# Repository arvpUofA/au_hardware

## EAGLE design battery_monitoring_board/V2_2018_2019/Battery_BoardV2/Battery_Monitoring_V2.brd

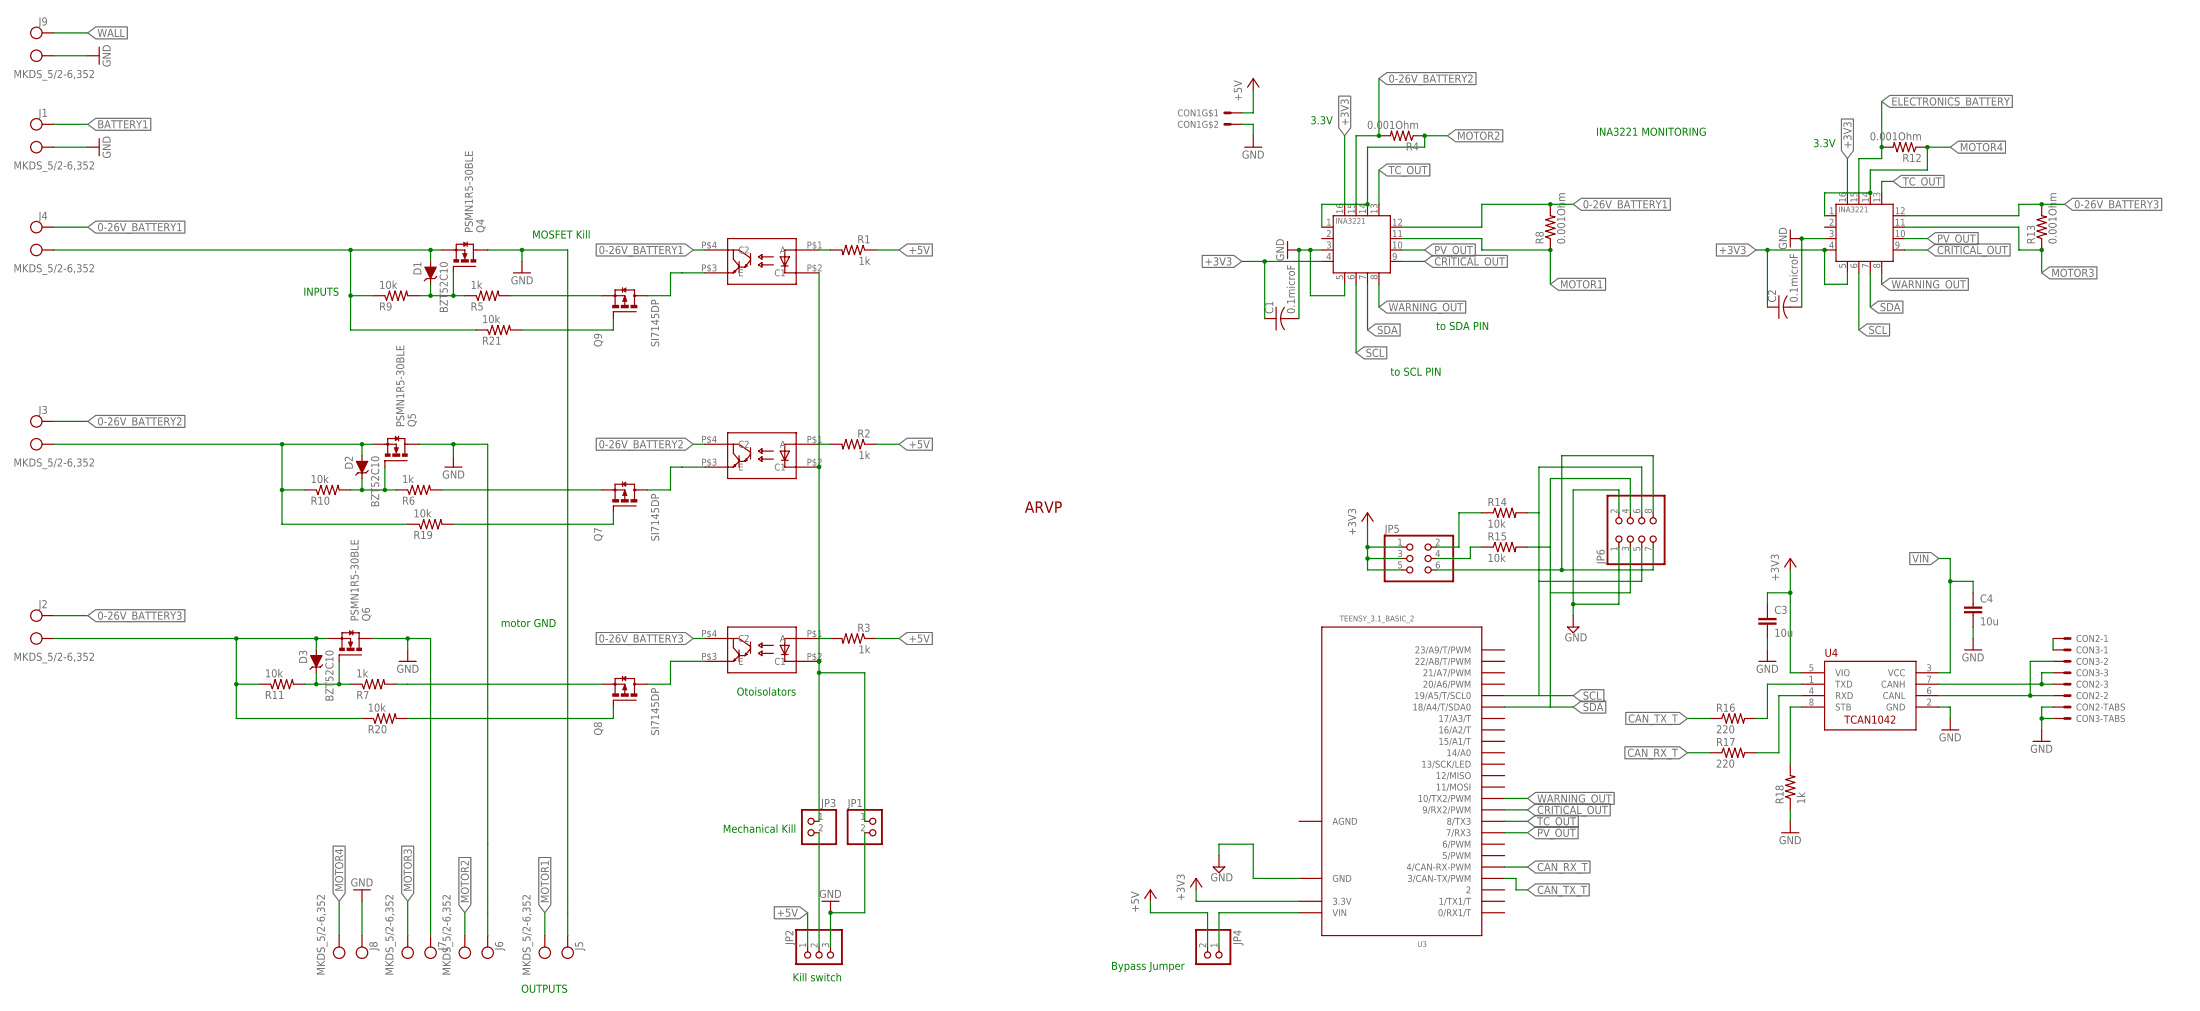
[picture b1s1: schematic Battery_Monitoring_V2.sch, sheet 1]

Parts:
ARVP1: ARVP_LOGO; ARVP
C1, C2: 0.1microF; C2012
C3, C4: 10u; C0805
CON1: MOLEX_5566-2; 5566-2
CON2, CON3: SM03B-GHS-TB
D1, D2, D3: BZT52C10; SOD-123
J1, J2, J3, J4, J5, J6, J7, J8, J9: MKDS_5/2-6,352; MKDS_5/2-6,35
JP1, JP3, JP4: PINHD-1X2; 1X02
JP2: PINHD-1X3; 1X03
JP5: PINHD-2X3; 2X03
JP6: PINHD-2X4; 2X04
Q1, Q2, Q3: TCLD1000CT; SOP-4L
Q4, Q5, Q6: PSMN1R5-30BLE; SOT404/D2PAK
Q7, Q8, Q9: SI7145DP; SO-8/PPAK/TEST; MPN SI7145DP-T1-GE3
R1, R2, R3, R18: 1k; R0805
R4, R8, R12, R13: 0.001Ohm; 3920
R5, R6, R7: 1k; M1206
R9, R10, R11: 10k; M1206
R14, R15: 10k; R1206
R16, R17: 220; R0805
R19, R20, R21: 10k; M1206; MPN RC0603FR-0710KL
U1, U2: INA3221.; HVQFN16_4X4
U3: TEENSY_3.1_BASIC_2
U4: TCAN1042HVDR; SO-8

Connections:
0-26V_BATTERY1: J4.2 (KL1), Q1.P$4 (C2), R8.P$2 (2), U1.12 (IN+1)
0-26V_BATTERY2: J3.2 (KL1), Q2.P$4 (C2), R4.P$2 (2), U1.15 (IN+2)
0-26V_BATTERY3: J2.2 (KL1), Q3.P$4 (C2), R13.P$2 (2), U2.12 (IN+1)
+3V3: C1.1, C2.1, C3.1, JP5.1, JP5.3, JP5.5, U1.4 (VS), U1.16 (VPU), U2.4 (VS), U2.5 (A0), U2.16 (VPU), U3.3.3V, U4.5 (VIO)
+5V: CON1.1, JP2.1, JP4.2, R1.1, R2.1, R3.1; also elsewhere on the board
AGND: U3.AGND
BATT1GND: D1.P$2 (A), J4.1 (KL), Q4.3S (S), R9.1, R21.1
BATT2GND: D2.P$2 (A), J3.1 (KL), Q5.3S (S), R10.1, R19.1
BATT3GND: D3.P$2 (A), J2.1 (KL), Q6.3S (S), R11.1, R20.1
BATTERY1: J1.2 (KL1); also elsewhere on the board
CANH1: CON2.P$3, CON3.P$3, U4.7 (CANH)
CANL1: CON2.P$2, CON3.P$2, U4.6 (CANL)
CANSH1: CON2.P$1, CON3.P$1
CAN_RX1: R17.2, U4.4 (RXD)
CAN_RX_T: R17.1, U3.4 (4/CAN-RX-PWM)
CAN_TX2: R16.2, U4.1 (TXD)
CAN_TX_T: R16.1, U3.3 (3/CAN-TX/PWM)
CRITICAL_OUT: U1.9 (CRITICAL), U2.9 (CRITICAL), U3.9 (9/RX2/PWM)
E1: Q1.P$3 (E), Q9.D@1 (D), Q9.D@2 (D), Q9.D@3 (D), Q9.D@4 (D), Q9.D@5 (D)
E2: Q2.P$3 (E), Q7.D@1 (D), Q7.D@2 (D), Q7.D@3 (D), Q7.D@4 (D), Q7.D@5 (D)
E3: Q3.P$3 (E), Q8.D@1 (D), Q8.D@2 (D), Q8.D@3 (D), Q8.D@4 (D), Q8.D@5 (D)
ELECTRONICS_BATTERY: R12.P$2 (2), U2.15 (IN+2); also elsewhere on the board
GND: C1.2, C2.2, C3.2, C4.2, CON1.2, CON2.P$4, CON2.P$5, CON3.P$4, CON3.P$5, J1.1 (KL), J5.2 (KL1), J6.2 (KL1), J7.2 (KL1), J8.2 (KL1), J9.1 (KL), JP1.2, JP2.3, JP6.1, JP6.2, Q4.2D (D), Q5.2D (D), Q6.2D (D), R18.1, U1.3 (GND), U1.5 (A0), U2.3 (GND), U3.GND, U4.2 (GND); also elsewhere on the board
I2C_3V1: JP5.6, JP6.7, JP6.8
MG1: D1.P$1 (C), Q4.1G (G), R5.1, R9.2
MG2: D2.P$1 (C), Q5.1G (G), R6.1, R10.2
MG3: D3.P$1 (C), Q6.1G (G), R7.1, R11.2
MOTOR1: J5.1 (KL), R8.P$1 (1), U1.11 (IN-1)
MOTOR2: J6.1 (KL), R4.P$1 (1), U1.1 (IN-3), U1.14 (IN-2)
MOTOR3: J7.1 (KL), R13.P$1 (1), U2.11 (IN-1)
MOTOR4: J8.1 (KL), R12.P$1 (1), U2.1 (IN-3), U2.14 (IN-2)
unnamed: Q1.P$1 (A), R1.2
unnamed: Q2.P$1 (A), R2.2
unnamed: Q3.P$1 (A), R3.2
unnamed: JP1.1, JP3.1, Q1.P$2 (C1), Q2.P$2 (C1), Q3.P$2 (C1)
unnamed: JP2.2, JP3.2
unnamed: Q7.G, R19.2
unnamed: Q8.G, R20.2
unnamed: Q9.G, R21.2
unnamed: Q9.S@1 (S), Q9.S@2 (S), Q9.S@3 (S), R5.2
unnamed: Q8.S@1 (S), Q8.S@2 (S), Q8.S@3 (S), R7.2
unnamed: Q7.S@1 (S), Q7.S@2 (S), Q7.S@3 (S), R6.2
PV_OUT: U1.10 (PV), U2.10 (PV), U3.7 (7/RX3)
SCL: JP6.5, JP6.6, R14.2, U1.6 (SCL), U2.6 (SCL), U3.19/A5 (19/A5/T/SCL0)
SCL_3V1: JP5.2, R14.1
SDA: JP6.3, JP6.4, R15.2, U1.7 (SDA), U2.7 (SDA), U3.18/A4 (18/A4/T/SDA0)
SDA_3V1: JP5.4, R15.1
STB1: R18.2, U4.8 (STB)
TC_OUT: U1.13 (TC), U2.13 (TC), U3.8 (8/TX3)
VIN: C4.1, JP4.1, U3.VIN, U4.3 (VCC)
WALL: J9.2 (KL1); also elsewhere on the board
WARNING_OUT: U1.8 (WARNING), U2.8 (WARNING), U3.10 (10/TX2/PWM)

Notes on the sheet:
3.3V
Kill switch
motor GND
INPUTS
INA3221 MONITORING
Otoisolators
OUTPUTS
MOSFET Kill
to SDA PIN
to SCL PIN
Mechanical Kill
Bypass Jumper

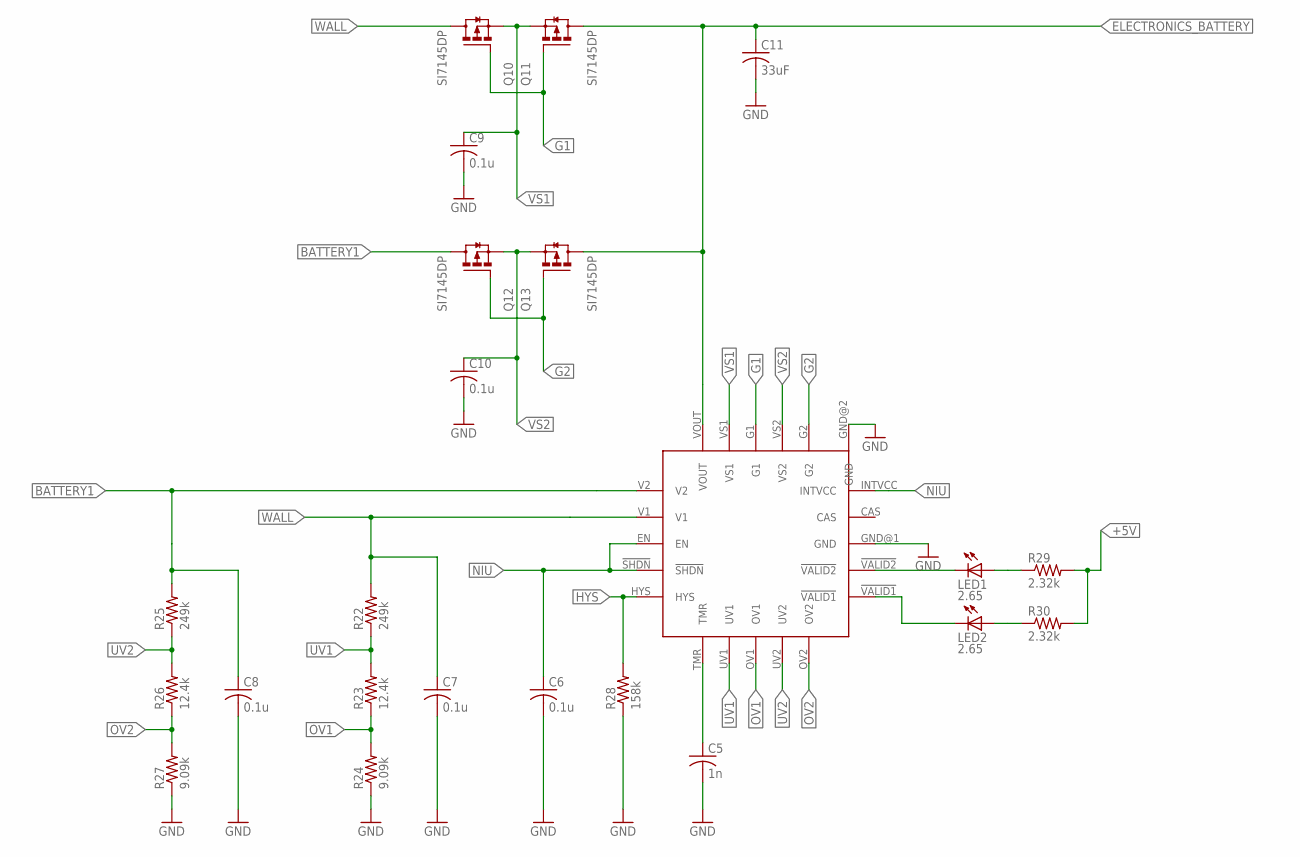
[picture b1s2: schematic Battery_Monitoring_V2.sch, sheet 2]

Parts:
C5: 1n; C0805
C6, C7, C8, C9, C10: 0.1u; C0805
C11: 33uF; C1206
LED1, LED2: 2.65; SML0805
Q10, Q11, Q12, Q13: SI7145DP; SO-8/PPAK/TEST
R22, R25: 249k; R1206
R23, R26: 12.4k; R0805
R24, R27: 9.09k; R0805
R28: 158k; R0805
R29, R30: 2.32k; R0805
U5: LTC4418; 20-QFN(4X4)

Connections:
!VALID1: LED2.C, U5.!VALID1
!VALID2: LED1.C, U5.!VALID2
+5V: R29.2, R30.2; also elsewhere on the board
BATTERY1: C8.1, Q12.D@1 (D), Q12.D@2 (D), Q12.D@3 (D), Q12.D@4 (D), Q12.D@5 (D), R25.2, U5.V2; also elsewhere on the board
ELECTRONICS_BATTERY: C11.1, Q11.D@1 (D), Q11.D@2 (D), Q11.D@3 (D), Q11.D@4 (D), Q11.D@5 (D), Q13.D@1 (D), Q13.D@2 (D), Q13.D@3 (D), Q13.D@4 (D), Q13.D@5 (D), U5.VOUT; also elsewhere on the board
G1: Q10.G, Q11.G, U5.G1
G2: Q12.G, Q13.G, U5.G2
GND: C5.2, C6.2, C7.2, C8.2, C9.2, C10.2, C11.2, R24.1, R27.1, R28.1, U5.GND@1 (GND), U5.GND@2 (GND); also elsewhere on the board
HYS: R28.2, U5.HYS
unnamed: LED1.A, R29.1
unnamed: LED2.A, R30.1
unnamed: C5.1, U5.TMR
NIU: C6.1, U5.!SHDN, U5.EN, U5.INTVCC
OV1: R23.1, R24.2, U5.OV1
OV2: R26.1, R27.2, U5.OV2
UV1: R22.1, R23.2, U5.UV1
UV2: R25.1, R26.2, U5.UV2
VS1: C9.1, Q10.S@1 (S), Q10.S@2 (S), Q10.S@3 (S), Q11.S@1 (S), Q11.S@2 (S), Q11.S@3 (S), U5.VS1
VS2: C10.1, Q12.S@1 (S), Q12.S@2 (S), Q12.S@3 (S), Q13.S@1 (S), Q13.S@2 (S), Q13.S@3 (S), U5.VS2
WALL: C7.1, Q10.D@1 (D), Q10.D@2 (D), Q10.D@3 (D), Q10.D@4 (D), Q10.D@5 (D), R22.2, U5.V1; also elsewhere on the board

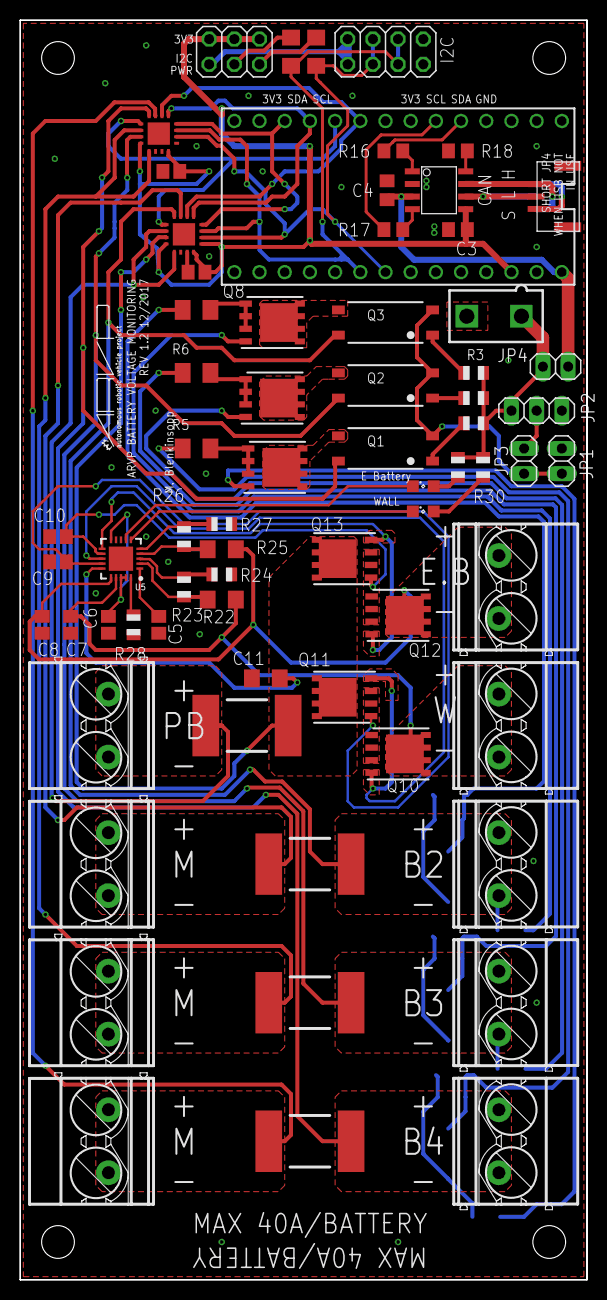
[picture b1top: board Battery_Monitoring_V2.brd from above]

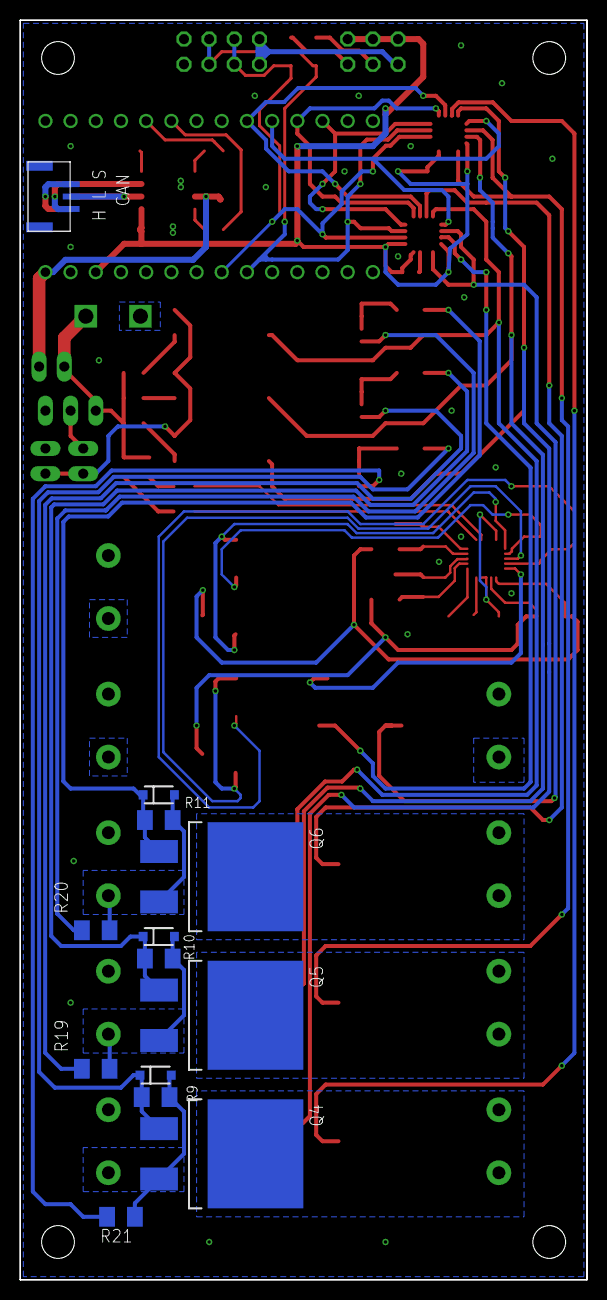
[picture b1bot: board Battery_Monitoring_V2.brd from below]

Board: 2 copper layers, 57.2 x 127.0 mm, 89 parts (13 on the bottom side), 66 nets.

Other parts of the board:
U$9: LETTER_P
U$15: DOCFIELD
U$18, U$24, U$25, U$26: STAND-OFF

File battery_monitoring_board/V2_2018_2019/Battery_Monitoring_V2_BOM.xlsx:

Teensy+i2c+CAN part list
Shematic Reference Number | Part Description | Manufacturer Part Number | Datasheet | Price | Quantity Required | On hand | Quantity To Buy | Total Cost | Customer Reference
JP5 | DIL VERTICAL PC TAIL PIN HEADER 2x3 | M20-9980345 | https://cdn.harwin.com/pdfs/M20-998.pdf | 0.34799999999999998 | 1 |  | 1 | 0.34799999999999998 | BATT_MON
JP6 | DIL VERTICAL PC TAIL PIN HEADER 2x4 | M20-9980445 | https://cdn.harwin.com/pdfs/M20-998.pdf | 0.48 | 1 |  | 1 | 0.48 | BATT_MON
R14, R15 | RES SMD 10K OHM 1% 1/4W 1206 | RC1206FR-0710KL | http://www.yageo.com/documents/recent/PYu-RC_Group_51_RoHS_L_7.pdf | 4.7E-2 | 2 |  | 2 | 9.4E-2 | BATT_MON
R16, R17 | RES SMD 220 OHM 1% 1/8W 0805 | RC0805FR-07220RL | http://www.yageo.com/documents/recent/PYu-RC_Group_51_RoHS_L_7.pdf | 3.1E-2 | 2 |  | 2 | 6.2E-2 | BATT_MON
R18 | RES SMD 1K OHM 1% 1/8W 0805 | RC0805FR-071KL | http://www.yageo.com/documents/recent/PYu-RC_Group_51_RoHS_L_7.pdf | 3.4000000000000002E-2 | 1 |  | 1 | 3.4000000000000002E-2 | BATT_MON
C3, C4 | CAP CER 10UF 16V X7R 0805 | CL21B106KOQNNNG | http://www.samsungsem.com/kr/support/product-search/mlcc/CL2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 | 0.39 | 2 |  | 2 | 0.78 | BATT_MON
CON3 | CONN HEADER GH SIDE 3POS 1.25MM | SM03B-GHS-TB(LF)(SN) | http://www.jst-mfg.com/product/pdf/eng/eGH.pdf | 0.68 | 2 | 4 | 0 | 1.36 | BATT_MON
U4 | IC TXRX CAN FAULT PROT 8SOIC | TCAN1042HVDRQ1 | http://www.ti.com/lit/ds/symlink/tcan1042hgv-q1.pdf | 2.0499999999999998 | 1 |  | 1 | 2.0499999999999998 | BATT_MON | Part appears in multiple lists on this board
CON1 | CONN HEADER 2POS 4.2MM VERT TIN | 39281023 | http://www.molex.com/pdm_docs/sd/039281023_sd.pdf | 0.83 | 1 |  | 1 | 0.83 | BATT_MON
JP4 | SIL VERTICAL PC TAIL PIN HEADER 1x2 | M20-9990245 | https://cdn.harwin.com/pdfs/M20-999.pdf | 0.2 | 1 |  | 1 | 0.2 | BATT_MON | We have these parts on hand
Teensy | CONN HEADER FMALE 14POS .1" GOLD | PPPC141LFBN-RC | http://www.sullinscorp.com/drawings/78_P(N)PxCxxxLFBN-RC,_10492-H.pdf | 1.28 | 2 |  | 2 | 2.56 | BATT_MON
Battery Monitoring part List
Shematic Reference Number | Part Description | Manufacturer Part Number | Datasheet | Price | Quantity Required | On hand | Quantity To Buy | Total Cost | Customer Reference
U1, U2 | IC CURRENT SHUNT MONITOR 16VQFN | INA3221AIRGVR | http://www.ti.com/lit/ds/symlink/ina3221.pdf | 5.39 | 2 |  | 2 | 10.78 | BATT_MON
R4, R8, R12, R13 | RES 0.001 OHM 1% 5W 3920 | HCS3920FT1L00 | https://www.seielect.com/catalog/sei-hcs.pdf | 2.5099999999999998 | 4 |  | 4 | 10.039999999999999 | BATT_MON
Q4, Q5, Q6 | MOSFET N-CH 30V 120A D2PAK | PSMN1R5-30BLEJ | https://assets.nexperia.com/documents/data-sheet/PSMN1R5-30BLE.pdf | 4.63 | 3 |  | 3 | 13.89 | BATT_MON
Q1, Q2, Q3 | OPTOISOLTR 5KV DARLINGTON 4-SOP | TCLD1000 | http://www.vishay.com/docs/83516/tcld1000.pdf | 1.0900000000000001 | 3 |  | 3 | 3.2700000000000005 | BATT_MON
D1, D2, D3 | DIODE ZENER 10V 500MW SOD123 | BZT52C10-7-F | https://www.diodes.com/assets/Datasheets/ds18004.pdf | 0.32 | 3 |  | 3 | 0.96 | BATT_MON
C1, C2 | CAP CER 0.1UF 50V Y5V 0805 | CL21F104ZBCNNNC | https://media.digikey.com/pdf/Data%20Sheets/Samsung%20PDFs/C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 | 0.14000000000000001 | 2 | 7 | 0 | 0.28000000000000003 | BATT_MON
R1, R2, R3 | RES SMD 1K OHM 5% 1/8W 0805 | RC2012J102CS | http://www.samsungsem.com/kr/support/product-search/chip-res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 | 0.15 | 3 |  | 3 | 0.44999999999999996 | BATT_MON
R5, R6, R7 | RES SMD 1K OHM 5% 1/4W 1206 | RC3216J102CS | http://www.samsungsem.com/kr/support/product-search/chip-res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 | 0.15 | 3 | 16 | 0 | 0.44999999999999996 | BATT_MON
R9, R10, R11 | RES SMD 10K OHM 5% 1/4W 1206 | RC3216J103CS | http://www.samsungsem.com/kr/support/product-search/chip-res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 | 0.15 | 3 |  | 3 | 0.44999999999999996 | BATT_MON
JP1, JP3 | CONN HEADER FEMALE 2POS .1" GOLD | PPPC021LFBN-RC | http://sullinscorp.com/catalogs/101_PAGE114-115_.100_FEMALE_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 | 0.45 | 2 |  | 2 | 0.9 | BATT_MON
JP2 | CONN HEADER FEMALE 3POS .1" GOLD | PPPC031LFBN-RC | http://sullinscorp.com/catalogs/101_PAGE114-115_.100_FEMALE_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 | 0.51 | 1 |  | 1 | 0.51 | BATT_MON
J1-J9 | CONN TERM BLOCK 2POS 6.35MM PCB | 1714955 | https://media.digikey.com/pdf/Data%20Sheets/Phoenix%20Contac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 | 2.11 | 9 |  | 9 | 18.989999999999998 | BATT_MON
Hotswap Circuit
Shematic Reference Number | Part Description | Manufacturer Part Number | Datasheet | Price | Quantity Required | On hand | Quantity To Buy | Total Cost | Customer Reference
U5 | IC CTRLR DUAL PWRPATH 20QFN | LTC4418IUF#PBF | LTC4418IUF#PBF | 9.23 | 1 |  | 1 | 9.23 | BATT_MON
Q10,Q11,Q12,Q13 | MOSFET P-CH 30V 60A PPAK SO-8 | SI7145DP-T1-GE3 | http://www.vishay.com/docs/64814/si7145dp.pdf | 3.68 | 4 | 3 | 1 | 14.72 | BATT_MON
LED1,LED2 | LED BLUE CLEAR 2012 SMD | APTD2012LQBC/D | http://www.kingbrightusa.com/images/catalog/SPEC/APTD2012LQB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 | 0.93 | 2 |  | 2 | 1.86 | BATT_MON
R22,R25 | RES SMD 249K OHM 1% 1/4W 1206 | RC1206FR-07249KL | http://www.yageo.com/documents/recent/PYu-RC_Group_51_RoHS_L_9.pdf | 0.15 | 2 |  | 2 | 0.3 | BATT_MON
R23,R26 | RES 12.4K OHM 1% 1/4W 0805 | RNCP0805FTD12K4 | https://www.seielect.com/Catalog/SEI-rncp.pdf | 0.1 | 2 |  | 2 | 0.2 | BATT_MON
R24,R27 | RES 9.09K OHM 1% 1/4W 0805 | RNCP0805FTD9K09 | https://www.seielect.com/Catalog/SEI-rncp.pdf | 0.1 | 2 |  | 2 | 0.2 | BATT_MON
R28 | RES SMD 158K OHM 0.5% 1/4W 0805 | ERJ-PB6D1583V | https://industrial.panasonic.com/cdbs/www-data/pdf/RDM0000/A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 | 0.25 | 1 |  | 1 | 0.25 | BATT_MON
R29,R30 | RES 2.32K OHM 1% 1/4W 0805 | RNCP0805FTD2K32 | https://www.seielect.com/Catalog/SEI-rncp.pdf | 0.1 | 2 |  | 2 | 0.2 | BATT_MON
C6,C7,C8,C9,C10 | CAP CER 0.1UF 50V X7R 0805 | 08055C104J4T2A | http://datasheets.avx.com/AutoMLCC.pdf | 0.27 | 5 |  | 5 | 1.35 | BATT_MON
C5 | CAP CER 1000PF 25V X7R 0805 | VJ0805Y102JXXPW1BC | https://www.vishay.com/docs/28548/vjw1bcbascomseries.pdf | 0.34 | 1 |  | 1 | 0.34 | BATT_MON
C11 | CAP CER 33UF 25V X5R 1206 | C3216X5R1E336M160AC | https://product.tdk.com/info/en/catalog/datasheets/mlcc_comm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 | 1.94 | 0 |  | 0 | 0 | BATT_MON
Reverse Polarity Protection Element Part List
Shematic Reference Number | Part Description | Manufacturer Part Number | Datasheet | Price | Quantity Required | On hand | Quantity To Buy | Total Cost | Customer Reference
R19, R20, R21 | RES SMD 10K OHM 5% 1/4W 1206 | RC3216J103CS | http://www.samsungsem.com/kr/support/product-search/chip-res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 | 0.15 | 3 |  | 3 | 0.44999999999999996 | BATT_MON
Q7, Q8, Q9 | MOSFET P-CH 30V 60A PPAK SO-8 | SI7145DP-T1-GE3 | http://www.vishay.com/docs/64814/si7145dp.pdf | 3.68 | 3 |  | 3 | 11.040000000000001 | BATT_MON
 |  |  |  |  | Total |  |  | 109.90800000000002

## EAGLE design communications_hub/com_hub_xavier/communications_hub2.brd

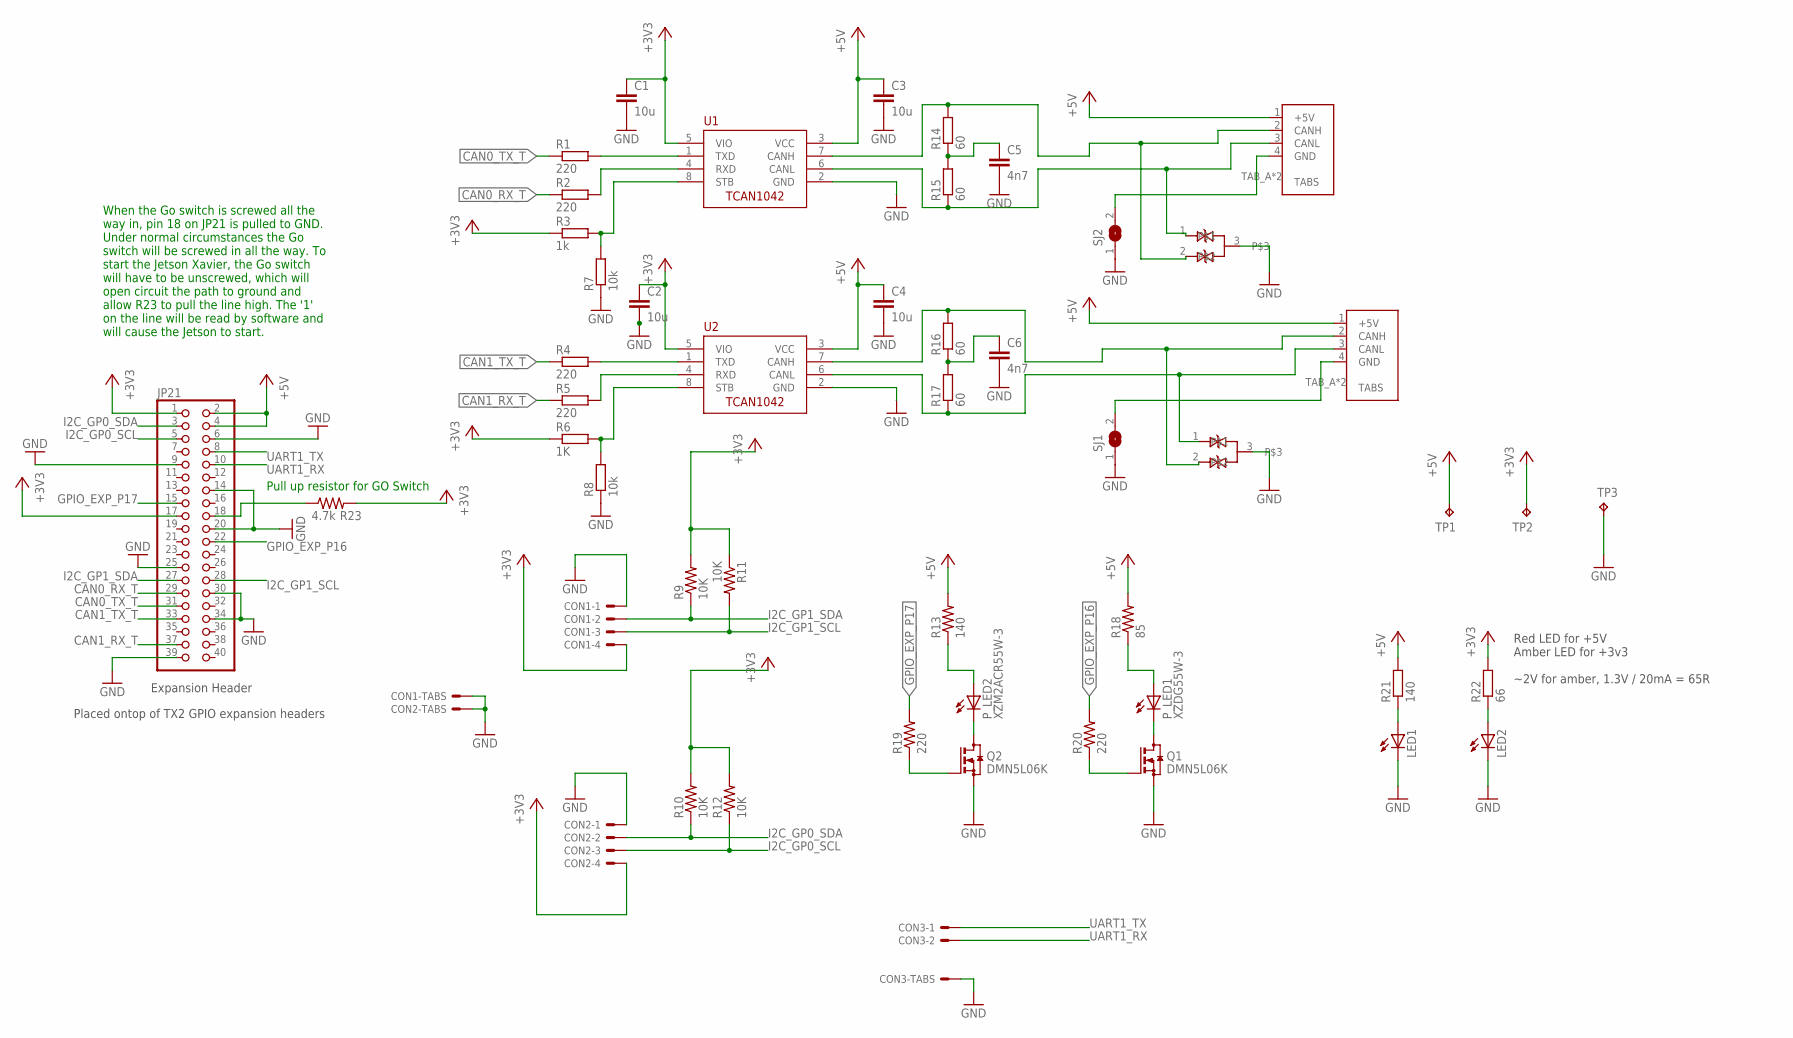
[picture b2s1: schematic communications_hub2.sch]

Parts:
C1, C2, C3, C4: 10u; C0805
C5, C6: 4n7; C0805
CON1, CON2: SM04B-GHS-TB
CON3: SM02B-GHS-TB
CON6, CON7: UAVCAN_MICRO; SM04B-GHS-TB
JP21: PINHD-2X20; 2X20
LED1, LED2: LEDSMT1206; 1206
P_LED1: XZDG55W-3; LED_1206
P_LED2: XZM2ACR55W-3; LED_1206
Q1, Q2: DMN5L06K; SOT23
R1, R2, R4, R5, R19, R20: 220; R0805
R3: 1k; R0805
R6: 1K; R0805
R7, R8: 10k; R0805
R9, R10, R11, R12: 10K; M1206
R13: 140; M1206
R14, R15, R16, R17: 60; R1206
R18: 85; M1206
R21: 140; R0805
R22: 66; R0805
R23: 4.7k; R0603
SJ1, SJ2: SJ
TP1, TP2, TP3: TPB2,54; B2,54
U1, U2: TCAN1042HVDR; SO-8
U$4, U$5: NUP2105L; SOT23

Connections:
+3V3: C1.1, C2.1, CON1.P$4, CON2.P$4, JP21.1, JP21.17, R3.1, R6.1, R9.2, R10.2, R11.1, R12.2, R22.2, R23.2, TP2.TP, U1.5 (VIO), U2.5 (VIO)
+5V: C3.1, C4.1, CON6.1 (+5V), CON7.1 (+5V), JP21.2, JP21.4, R13.2, R18.2, R21.2, TP1.TP, U1.3 (VCC), U2.3 (VCC)
CAN0_RX_T: JP21.29, R2.1
CAN0_TX_T: JP21.31, R1.1
CAN1_RX_T: JP21.37, R5.1
CAN1_TX_T: JP21.33, R4.1
GND: C1.2, C2.2, C3.2, C4.2, C5.2, C6.2, CON1.P$1, CON1.P$5, CON1.P$6, CON2.P$1, CON2.P$5, CON2.P$6, CON3.P$3, CON3.P$4, JP21.6, JP21.9, JP21.14, JP21.20, JP21.25, JP21.30, JP21.34, JP21.39, LED1.C, LED2.C, Q1.2 (S), Q2.2 (S), R7.1, R8.1, SJ1.1, SJ2.1, TP3.TP, U1.2 (GND), U2.2 (GND), U$4.3, U$5.3
GPIO_EXP_P16: JP21.22, R20.2
GPIO_EXP_P17: JP21.15, R19.2
I2C_GP0_SCL: CON2.P$3, JP21.5, R12.1
I2C_GP0_SDA: CON2.P$2, JP21.3, R10.1
I2C_GP1_SCL: CON1.P$3, JP21.28, R11.2
I2C_GP1_SDA: CON1.P$2, JP21.27, R9.1
unnamed: JP21.18, R23.1
unnamed: P_LED2.A, R13.1
unnamed: P_LED1.A, R18.1
unnamed: CON7.4 (GND), SJ1.2
unnamed: CON6.4 (GND), SJ2.2
unnamed: P_LED2.C, Q2.3 (D)
unnamed: P_LED1.C, Q1.3 (D)
unnamed: Q2.1 (G), R19.1
unnamed: Q1.1 (G), R20.1
unnamed: LED1.A, R21.1
unnamed: LED2.A, R22.1
unnamed: C5.1, R14.1, R15.2
unnamed: C6.1, R16.1, R17.2
unnamed: CON7.2 (CANH), R16.2, U2.7 (CANH), U$5.2
unnamed: CON7.3 (CANL), R17.1, U2.6 (CANL), U$5.1
unnamed: CON6.2 (CANH), R14.2, U1.7 (CANH), U$4.2
unnamed: CON6.3 (CANL), R15.1, U1.6 (CANL), U$4.1
unnamed: R1.2, U1.1 (TXD)
unnamed: R2.2, U1.4 (RXD)
unnamed: R3.2, R7.2, U1.8 (STB)
unnamed: R4.2, U2.1 (TXD)
unnamed: R5.2, U2.4 (RXD)
unnamed: R6.2, R8.2, U2.8 (STB)
UART1_RX: CON3.P$2, JP21.10
UART1_TX: CON3.P$1, JP21.8

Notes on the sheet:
Placed ontop of TX2 GPIO expansion headers
Expansion Header
Red LED for +5V Amber LED for +3v3 ~2V for amber, 1.3V / 20mA = 65R
Pull up resistor for GO Switch
When the Go switch is screwed all the way in, pin 18 on JP21 is pulled to GND. Under normal circumstances the Go switch will be screwed in all the way. To start the Jetson Xavier, the Go switch will have to be unscrewed, which will open circuit the path to ground and allow R23 to pull the line high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

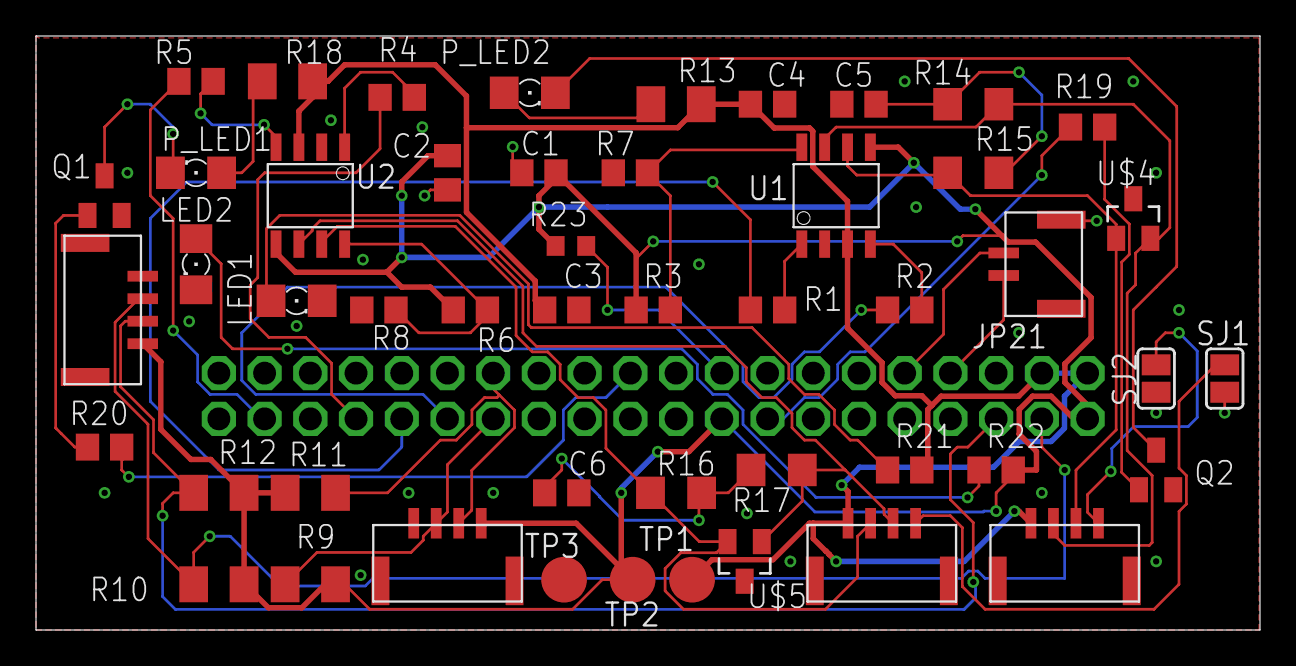
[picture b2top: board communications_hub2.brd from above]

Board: 2 copper layers, 68.0 x 33.0 mm, 50 parts (1 on the bottom side), 38 nets.

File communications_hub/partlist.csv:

Partlist

Exported from communication-hub.sch at 2017-12-03 1:42 PM

EAGLE Version 8.4.3 Copyright (c) 1988-2017 Autodesk, Inc.

Assembly variant: 

Part         Value          Device       Package      Library       Sheet

C1           10u            C-EUC0805    C0805        resistor      1
C2           10u            C-EUC0805    C0805        resistor      1
C3           10u            C-EUC0805    C0805        resistor      1
C4           10u            C-EUC0805    C0805        resistor      1
C5           4n7            C-EUC0805    C0805        resistor      1
C6           4n7            C-EUC0805    C0805        resistor      1
CON1         SM04B-GHS-TB   SM04B-GHS-TB SM04B-GHS-TB ARVP          1
CON2         SM04B-GHS-TB   SM04B-GHS-TB SM04B-GHS-TB ARVP          1
CON3         SM02B-GHS-TB   SM02B-GHS-TB SM02B-GHS-TB ARVP          1
CON4         SM04B-GHS-TB   SM04B-GHS-TB SM04B-GHS-TB ARVP          1
CON5         SM04B-GHS-TB   SM04B-GHS-TB SM04B-GHS-TB ARVP          1
GPIO_EXP_P16                LED_E        LED_1206     eagle-ltspice 1
GPIO_EXP_P17                LED_E        LED_1206     eagle-ltspice 1
JP3                         JP1Q         JP1          jumper        1
JP4                         JP1Q         JP1          jumper        1
JP5                         JP1Q         JP1          jumper        1
JP6                         JP1Q         JP1          jumper        1
JP7                         JP1Q         JP1          jumper        1
JP8                         JP1Q         JP1          jumper        1
JP21                        PINHD-2X20   2X20         commhub       1
JP26                        PINHD-2X15   2X15         commhub       1
R1           220            R-EU_R0805   R0805        resistor      1
R2           220            R-EU_R0805   R0805        resistor      1
R3           1k             R-EU_R0805   R0805        resistor      1
R4           220            R-EU_R0805   R0805        resistor      1
R5           220            R-EU_R0805   R0805        resistor      1
R6           1K             R-EU_R0805   R0805        resistor      1
R7           10k            R-EU_R0805   R0805        resistor      1
R8           10k            R-EU_R0805   R0805        resistor      1
R9                          R-US_M1206   M1206        resistor      1
R10                         R-US_M1206   M1206        resistor      1
R11                         R-US_M1206   M1206        resistor      1
R12                         R-US_M1206   M1206        resistor      1
R13          2k4            R-US_M1206   M1206        resistor      1
R14          60             R-EU_R1206   R1206        resistor      1
R15          60             R-EU_R1206   R1206        resistor      1
R16          60             R-EU_R1206   R1206        resistor      1
R17          60             R-EU_R1206   R1206        resistor      1
R18          2k4            R-US_M1206   M1206        resistor      1
SJ1                         SJ           SJ           jumper        1
SJ2                         SJ           SJ           jumper        1
U1           TCAN1042HVDR   TCAN1042HVDR SO-8         ARVP          1
U2           TCAN1042HVDR   TCAN1042HVDR SO-8         ARVP          1

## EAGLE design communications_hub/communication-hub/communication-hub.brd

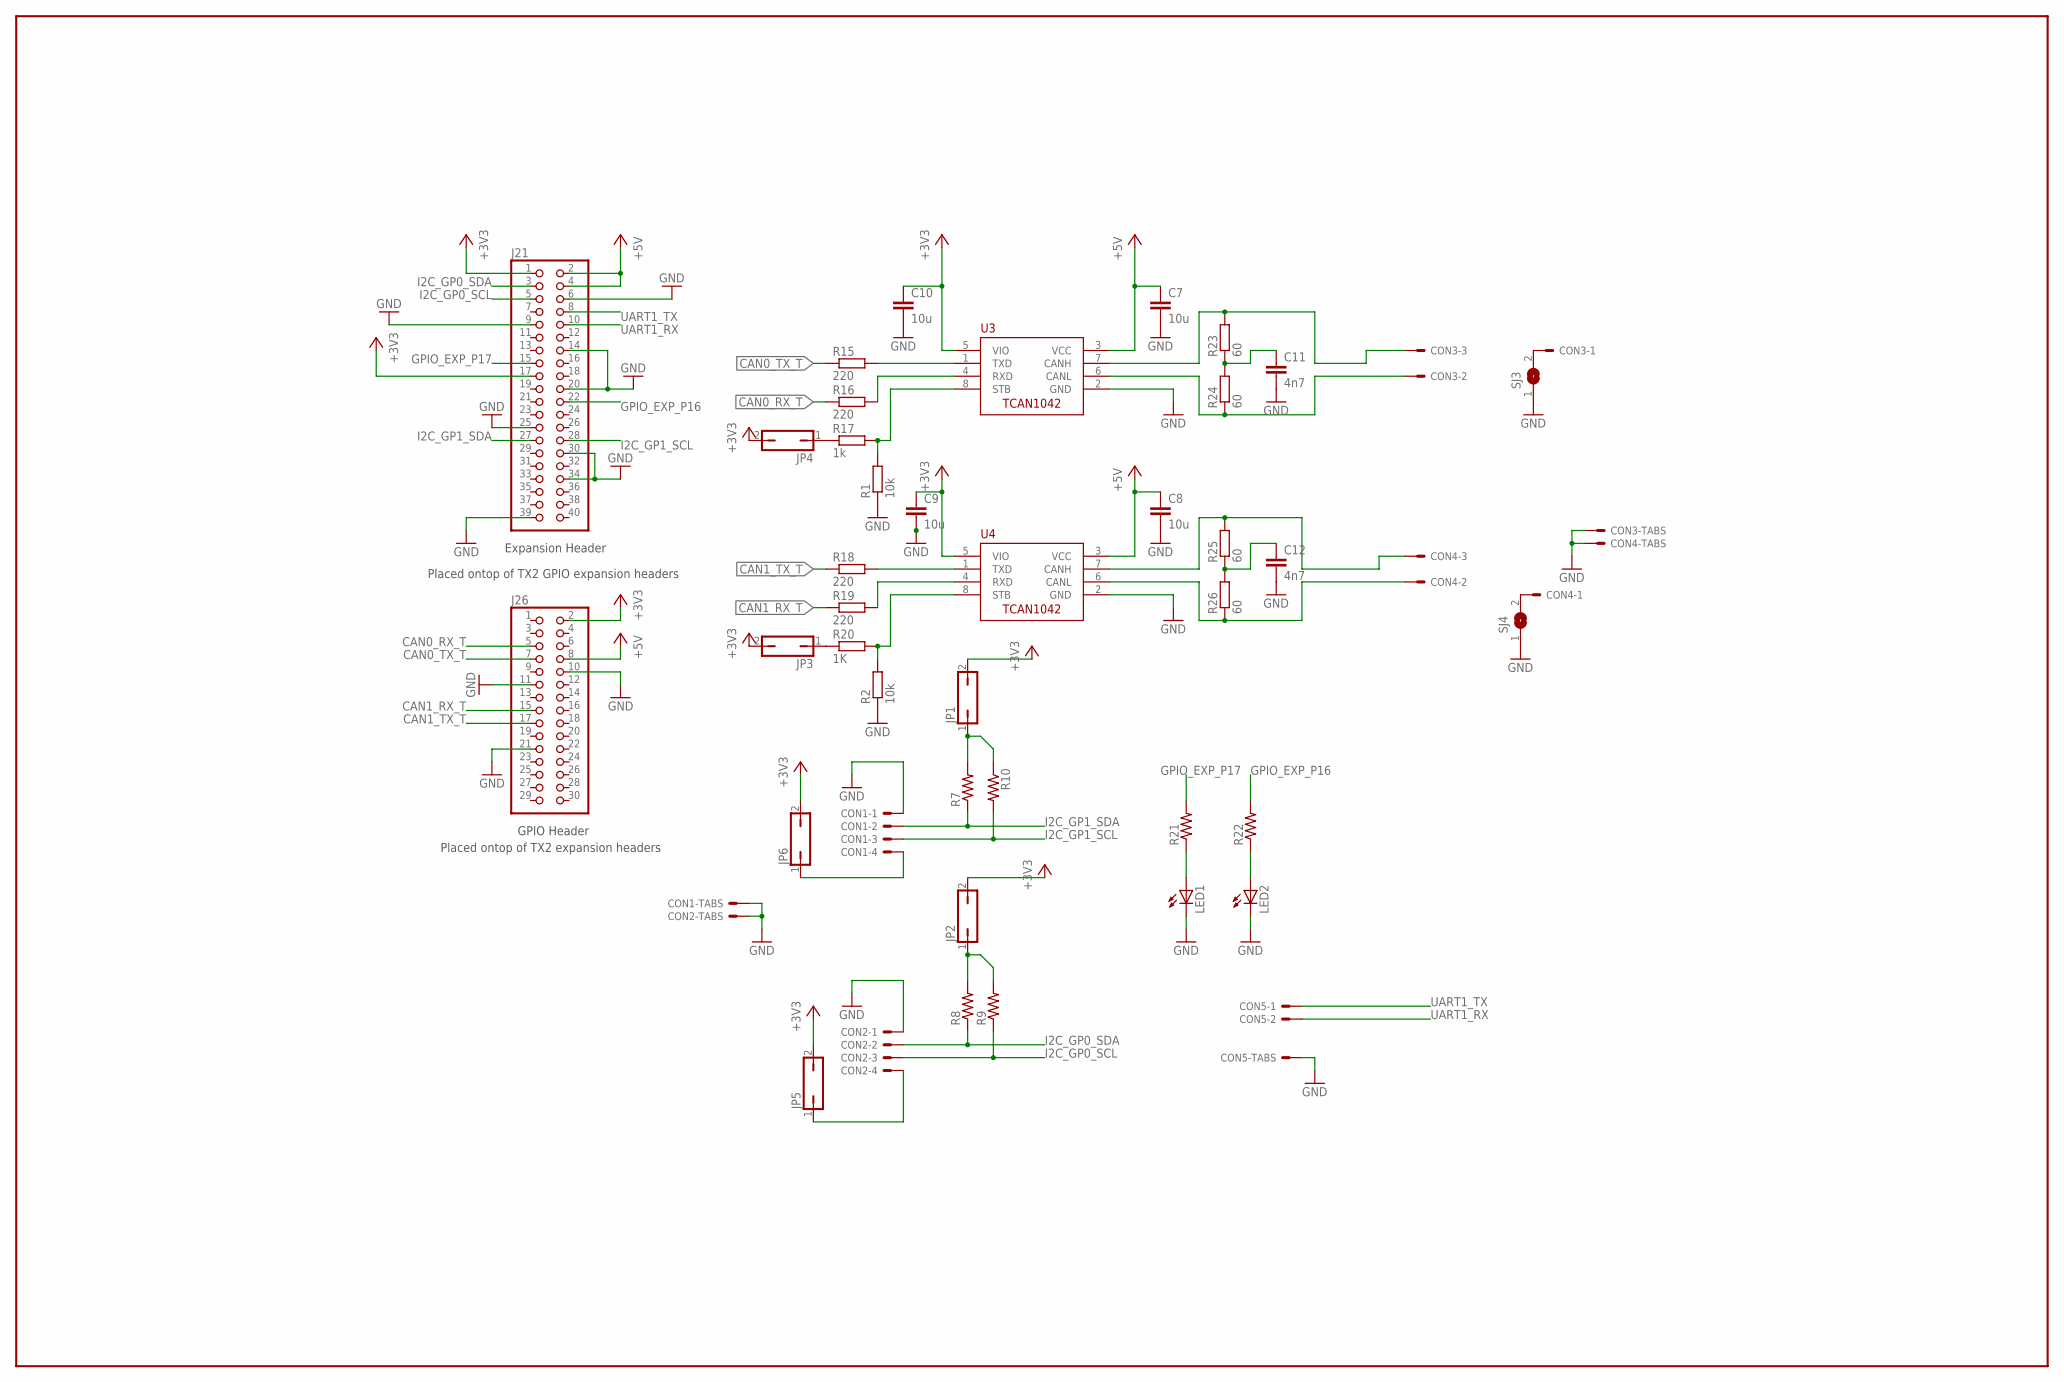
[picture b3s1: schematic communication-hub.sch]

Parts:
C7, C8, C9, C10: 10u; C0805
C11, C12: 4n7; C0805
CON1, CON2: SM04B-GHS-TB
CON3, CON4: SM03B-GHS-TB
CON5: SM02B-GHS-TB
J21: PINHD-2X20; 2X20
J26: PINHD-2X15; 2X15
JP1, JP2, JP3, JP4, JP5, JP6: JP1Q; JP1
LED1, LED2: LED_E; LED_1206
R1, R2: 10k; R0805
R7, R8, R9, R10, R21, R22: R-US_M1206; M1206
R15, R16, R18, R19: 220; R0805
R17: 1k; R0805
R20: 1K; R0805
R23, R24, R25, R26: 60; R1206
SJ3, SJ4: SJ
U3, U4: TCAN1042HVDR; SO-8

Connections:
+3V3: C9.1, C10.1, J21.1, J21.17, J26.2, JP1.2, JP2.2, JP3.2, JP4.2, JP5.2, JP6.2, U3.5 (VIO), U4.5 (VIO)
+5V: C7.1, C8.1, J21.2, J21.4, J26.8, U3.3 (VCC), U4.3 (VCC)
CAN0_RX_T: J26.5, R16.1
CAN0_TX_T: J26.7, R15.1
CAN1_RX_T: J26.15, R19.1
CAN1_TX_T: J26.17, R18.1
GND: C7.2, C8.2, C9.2, C10.2, C11.2, C12.2, CON1.P$1, CON1.P$5, CON1.P$6, CON2.P$1, CON2.P$5, CON2.P$6, CON3.P$4, CON3.P$5, CON4.P$4, CON4.P$5, CON5.P$3, CON5.P$4, J21.6, J21.9, J21.14, J21.20, J21.25, J21.30, J21.34, J21.39, J26.10, J26.11, J26.21, LED1.C, LED2.C, R1.1, R2.1, SJ3.1, SJ4.1, U3.2 (GND), U4.2 (GND)
GPIO_EXP_P16: J21.22, R22.2
GPIO_EXP_P17: J21.15, R21.2
I2C_GP0_SCL: CON2.P$3, J21.5, R9.1
I2C_GP0_SDA: CON2.P$2, J21.3, R8.1
I2C_GP1_SCL: CON1.P$3, J21.28, R10.2
I2C_GP1_SDA: CON1.P$2, J21.27, R7.1
unnamed: JP2.1, R8.2, R9.2
unnamed: JP1.1, R7.2, R10.1
unnamed: LED1.A, R21.1
unnamed: LED2.A, R22.1
unnamed: CON1.P$4, JP6.1
unnamed: CON2.P$4, JP5.1
unnamed: C11.1, R23.1, R24.2
unnamed: C12.1, R25.1, R26.2
unnamed: CON4.P$3, R25.2, U4.7 (CANH)
unnamed: CON4.P$2, R26.1, U4.6 (CANL)
unnamed: CON3.P$3, R23.2, U3.7 (CANH)
unnamed: CON3.P$2, R24.1, U3.6 (CANL)
unnamed: R15.2, U3.1 (TXD)
unnamed: R16.2, U3.4 (RXD)
unnamed: R1.2, R17.2, U3.8 (STB)
unnamed: R18.2, U4.1 (TXD)
unnamed: R19.2, U4.4 (RXD)
unnamed: R2.2, R20.2, U4.8 (STB)
unnamed: CON3.P$1, SJ3.2
unnamed: CON4.P$1, SJ4.2
unnamed: JP4.1, R17.1
unnamed: JP3.1, R20.1
UART1_RX: CON5.P$2, J21.10
UART1_TX: CON5.P$1, J21.8

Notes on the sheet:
Placed ontop of TX2 expansion headers
Placed ontop of TX2 GPIO expansion headers
GPIO Header
Expansion Header
